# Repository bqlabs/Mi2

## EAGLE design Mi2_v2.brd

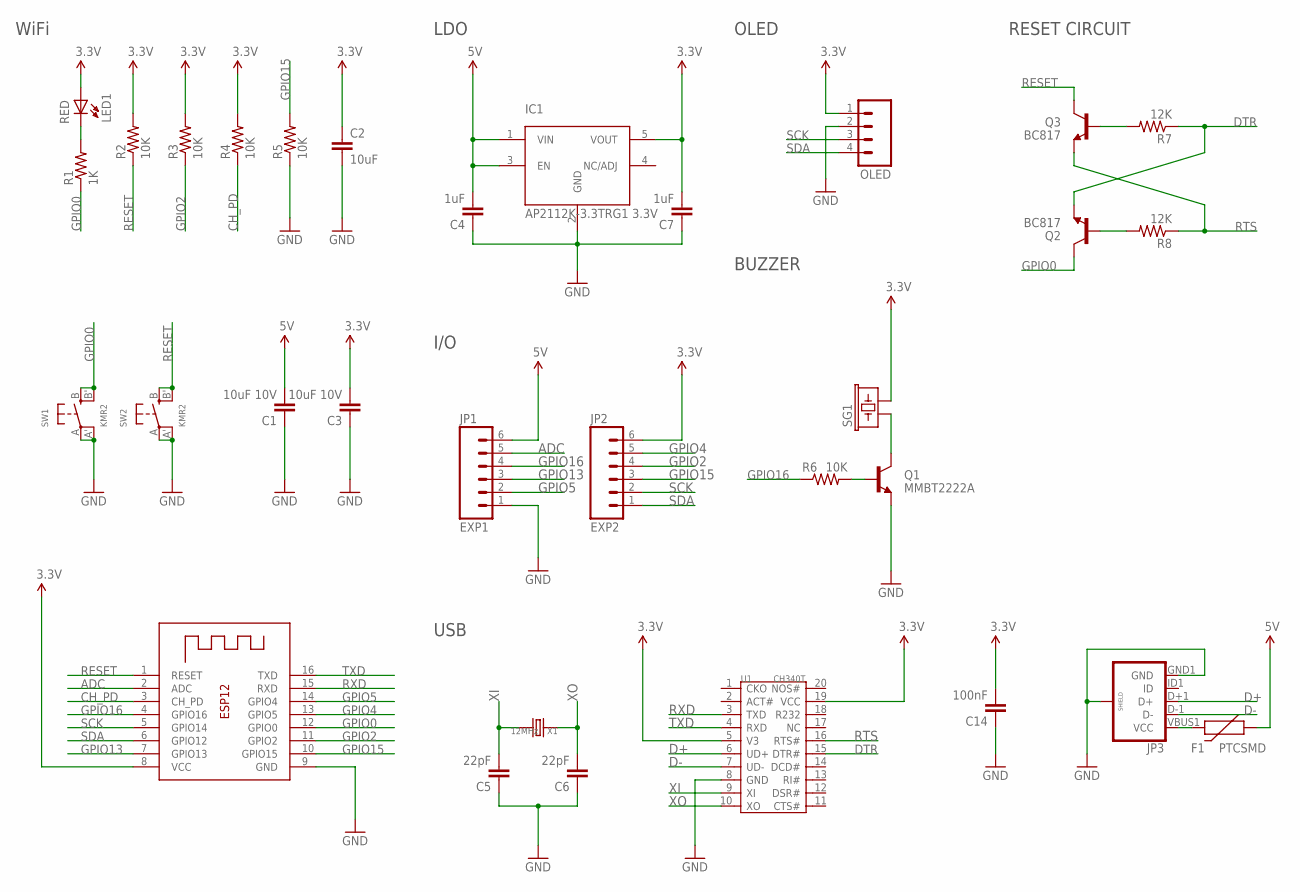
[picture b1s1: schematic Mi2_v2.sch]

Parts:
C1, C3: 10uF 10V; 0402-CAP
C2: 10uF; 0603-CAP
C4, C7: 1uF; 0402-CAP
C5, C6: 22pF; 0402-CAP
C14: 100nF; 0402-CAP
F1: PTCSMD; PTC-1206
IC1: AP2112K-3.3TRG1 3.3V; SOT23-5
JP1: EXP1; 1X06_LOCK
JP2: EXP2; 1X06_LOCK
JP3: USB_MICROB_PLUGCONN-11752; USB-B-MICRO-SMD_V03
LED1: RED; LED-0603_L
OLED: M04LOCK; 1X04_LOCK
Q1: MMBT2222A; SOT23-3
Q2, Q3: BC817; SOT23-3
R1: 1K; R0402
R2, R3, R4, R5: 10K; R0402
R6: 10K; 0402-RES
R7, R8: 12K; R0402
SG1: BUZZERSMD2; BUZZER-CCV
SW1, SW2: KMR2; BTN_KMR2_4.6X2.8
U1: CH340T; SSOP20
X1: 12MHz; 2P-SMD-5X3.2
X2: ESP-12

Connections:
3.3V: C2.1, C3.2, C7.2, C14.2, IC1.5 (VOUT), JP2.6, LED1.A, OLED.1, R2.2, R3.2, R4.2, SG1.- (2), U1.5 (V3), U1.19 (VCC), X2.8 (VCC)
5V: C1.2, C4.2, F1.1, IC1.1 (VIN), IC1.3 (EN), JP1.6
ADC: JP1.5, X2.2 (ADC)
CH_PD: R4.1, X2.3 (CH_PD)
D+: JP3.D+1 (D+), U1.6 (UD+)
D-: JP3.D-1 (D-), U1.7 (UD-)
DTR: Q2.2 (E), R7.1, U1.15 (DTR#)
GND: C1.1, C2.2, C3.1, C4.1, C5.1, C6.1, C7.1, C14.1, IC1.2 (GND), JP1.1, JP3.GND1 (GND), JP3.SHIELD1 (SHIELD), JP3.SHIELD2 (SHIELD), JP3.SHIELD3 (SHIELD), OLED.2, Q1.2 (E), R5.1, SW1.A, SW1.A' (P1), SW2.A, SW2.A' (P1), U1.8 (GND), X2.9 (GND)
GPIO0: Q2.3 (C), R1.1, SW1.B (S), SW1.B' (S1), X2.12 (GPIO0)
GPIO2: JP2.4, R3.1, X2.11 (GPIO2)
GPIO4: JP2.5, X2.13 (GPIO5)
GPIO5: JP1.2, X2.14 (GPIO4)
GPIO13: JP1.3, X2.7 (GPIO13)
GPIO15: JP2.3, R5.2, X2.10 (GPIO15)
GPIO16: JP1.4, R6.1, X2.4 (GPIO16)
unnamed: Q3.1 (B), R7.2
unnamed: LED1.C, R1.2
unnamed: Q2.1 (B), R8.2
unnamed: Q1.3 (C), SG1.+ (1)
unnamed: Q1.1 (B), R6.2
unnamed: F1.2, JP3.VBUS1 (VCC)
RESET: Q3.3 (C), R2.1, SW2.B (S), SW2.B' (S1), X2.1 (RESET)
RTS: Q3.2 (E), R8.1, U1.16 (RTS#)
RXD: U1.3 (TXD), X2.15 (RXD)
SCK: JP2.2, OLED.3, X2.5 (GPIO14)
SDA: JP2.1, OLED.4, X2.6 (GPIO12)
TXD: U1.4 (RXD), X2.16 (TXD)
XI: C5.2, U1.9 (XI), X1.2
XO: C6.2, U1.10 (XO), X1.1

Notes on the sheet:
WiFi
LDO
USB
OLED
I/O
BUZZER
RESET CIRCUIT

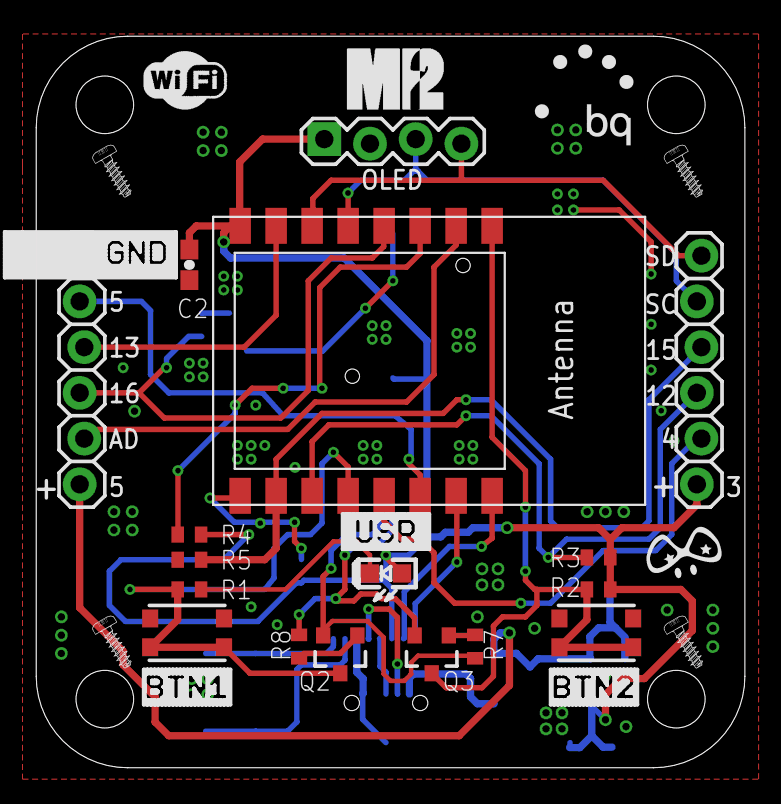
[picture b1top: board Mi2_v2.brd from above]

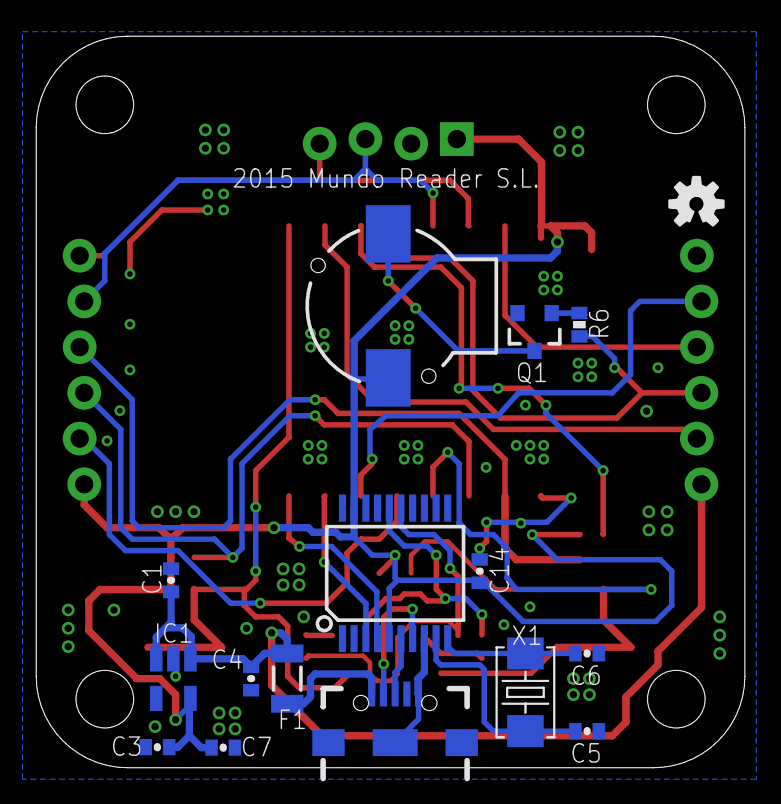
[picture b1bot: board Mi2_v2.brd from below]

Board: 2 copper layers, 39.4 x 40.6 mm, 45 parts (16 on the bottom side), 29 nets.

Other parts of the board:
LOGO1: OSHW-LOGOS; OSHW-LOGO-S
U$1: PIGHIXXX_LOGO
U$2: S_KICIK_GND_1
U$3: S_WIFI
U$4: S_BTN1
U$5: S_BTN2
U$6: S_USR
U$7: BQ_LOGO_SMALL
U$8, U$9, U$10, U$11: SCREW
U$12: MI2_LOGO

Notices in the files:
parts and their libraries:
SparkFun-Capacitors: Licensing: Creative Commons ShareAlike 4.0 International - https://creativecommons.org/licenses/by-sa/4.0
microbuilder: This work is placed in the public domain, and may be freely used for commercial and non-commercial work with the following conditions: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
